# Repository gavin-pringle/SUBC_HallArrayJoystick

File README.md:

# SUBC - Hall-Effect Sensor Array Joystick

## Use Case

- For use in pilot's joystick controlling pitch and yaw for [SUBC](subc.ca)'s 2023 human powered submarine.
- A 3D printed assembly is being designed to house and guide a magnet to travel along the up-down and left-right axes of the PCBA. This magnet is connected to a joystick handle that is contrained to move along these same axes. When the pilot positions the magnet in a certain direction the magnet activates the hall-effect sensors in that direction. The quad op-amp IC in the center of the PCB produces a weighted average of the hall-effect outputs for each direction, weighting greater the sensor further from the center. Each output from the op-amp IC is connected to its labelled output pin in the JST connector.
- This design allows for easier waterproofing by excluding the use of potentiometers.

## Technical Specifications

- Two layer PCB, 100x100mm.
- Uses eight [DRV5055 SMD linear hall-effect sensors](https://www.ti.com/lit/ds/symlink/drv5055.pdf).
- Uses an [SMD quad op-amp](https://www.ti.com/lit/ds/symlink/lm2902-n.pdf) to average both hall-effect outputs in each direction (up, down, left, right).
- Single six pin JST connector containing PWR, GND, and analog outputs for each direction.
- Since connector is only through-hole component, entire PCBA can be easily waterproofed with potting compound for use in submarine.
- Current revision has extra traces and pads for optionally adding trimmer pots to tune hall effect sensor weighting.

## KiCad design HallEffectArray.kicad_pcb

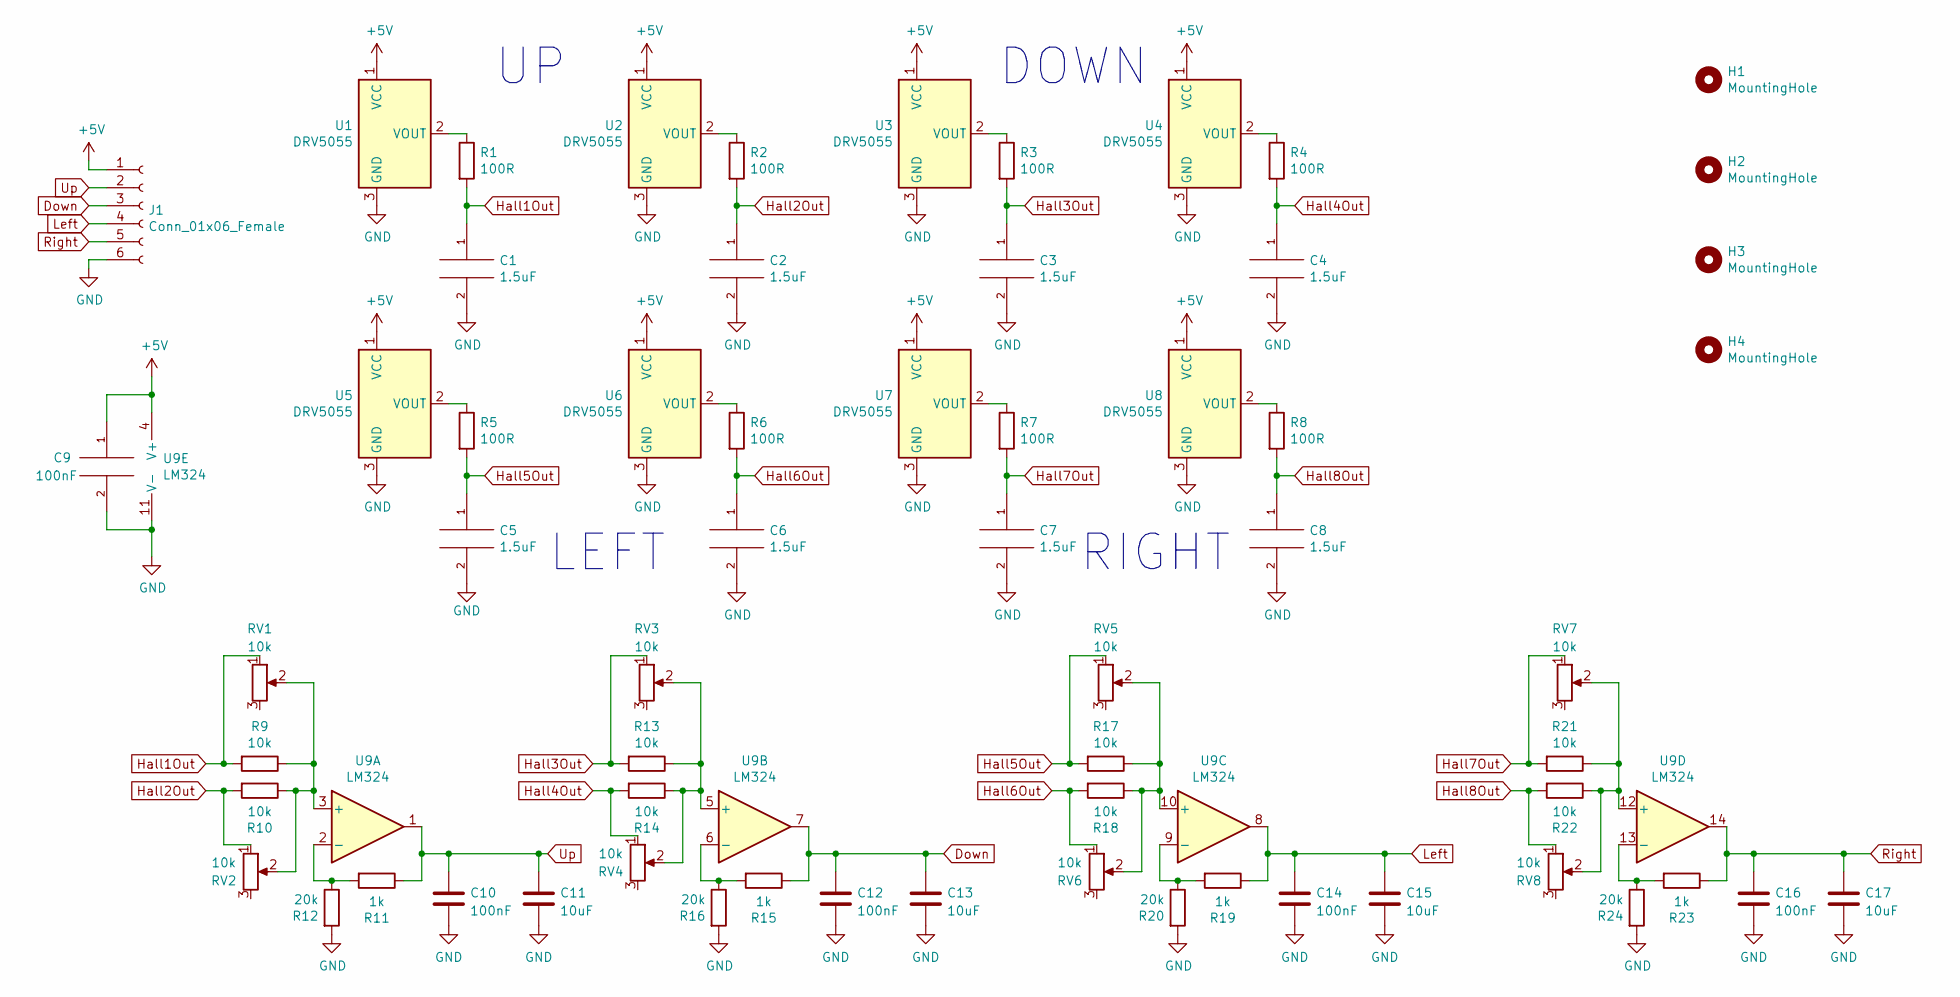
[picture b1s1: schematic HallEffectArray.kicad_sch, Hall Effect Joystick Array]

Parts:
C1, C2, C3, C4, C5, C6, C7, C8: 1.5uF; C_0805_2012Metric
C9, C10, C12, C14, C16: 100nF; C_0805_2012Metric
C11, C13, C15, C17: 10uF; C_0805_2012Metric
H1, H2, H3, H4: MountingHole; MountingHole_2.7mm_M2.5
J1: Conn_01x06_Female; JST_XH_B6B-XH-A_1x06_P2.50mm_Vertical
R1, R2, R3, R4, R5, R6, R7, R8: 100R; R_0805_2012Metric
R9, R10, R13, R14, R17, R18, R21, R22: 10k; R_0805_2012Metric
R11, R15, R19, R23: 1k; R_0805_2012Metric
R12, R16, R20, R24: 20k; R_0805_2012Metric
RV1, RV2, RV3, RV4, RV5, RV6, RV7, RV8: 10k; Potentiometer_Bourns_TC33X_Vertical
U1, U2, U3, U4, U5, U6, U7, U8: DRV5055; SOT-23
U9: LM324; SOIC-14_3.9x8.7mm_P1.27mm

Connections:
+5V: C9.1, J1.1, U1.1 (VCC), U2.1 (VCC), U3.1 (VCC), U4.1 (VCC), U5.1 (VCC), U6.1 (VCC), U7.1 (VCC), U8.1 (VCC), U9.4 (V+)
Down: C12.1, C13.1, J1.3, R15.1, U9.7
GND: C1.2, C2.2, C3.2, C4.2, C5.2, C6.2, C7.2, C8.2, C9.2, C10.2, C11.2, C12.2, C13.2, C14.2, C15.2, C16.2, C17.2, J1.6, R12.2, R16.2, R20.2, R24.2, U1.3 (GND), U2.3 (GND), U3.3 (GND), U4.3 (GND), U5.3 (GND), U6.3 (GND), U7.3 (GND), U8.3 (GND), U9.11 (V-)
Hall1Out: C1.1, R1.2, R9.2, RV1.1
Hall2Out: C2.1, R2.2, R10.2, RV2.1
Hall3Out: C3.1, R3.2, R13.2, RV3.1
Hall4Out: C4.1, R4.2, R14.2, RV4.1
Hall5Out: C5.1, R5.2, R17.2, RV5.1
Hall6Out: C6.1, R6.2, R18.2, RV6.1
Hall7Out: C7.1, R7.2, R21.2, RV7.1
Hall8Out: C8.1, R8.2, R22.2, RV8.1
Left: C14.1, C15.1, J1.4, R19.1, U9.8
unnamed: R1.1, U1.2 (VOUT)
unnamed: R2.1, U2.2 (VOUT)
unnamed: R3.1, U3.2 (VOUT)
unnamed: R4.1, U4.2 (VOUT)
unnamed: R5.1, U5.2 (VOUT)
unnamed: R6.1, U6.2 (VOUT)
unnamed: R7.1, U7.2 (VOUT)
unnamed: R8.1, U8.2 (VOUT)
unnamed: R9.1, R10.1, RV1.2, RV2.2, U9.3 (+)
unnamed: R11.2, R12.1, U9.2 (-)
unnamed: R13.1, R14.1, RV3.2, RV4.2, U9.5 (+)
unnamed: R15.2, R16.1, U9.6 (-)
unnamed: R17.1, R18.1, RV5.2, RV6.2, U9.10 (+)
unnamed: R19.2, R20.1, U9.9 (-)
unnamed: R21.1, R22.1, RV7.2, RV8.2, U9.12 (+)
unnamed: R23.2, R24.1, U9.13 (-)
Right: C16.1, C17.1, J1.5, R23.1, U9.14
Up: C10.1, C11.1, J1.2, R11.1, U9.1

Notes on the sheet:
DOWN
RIGHT
LEFT

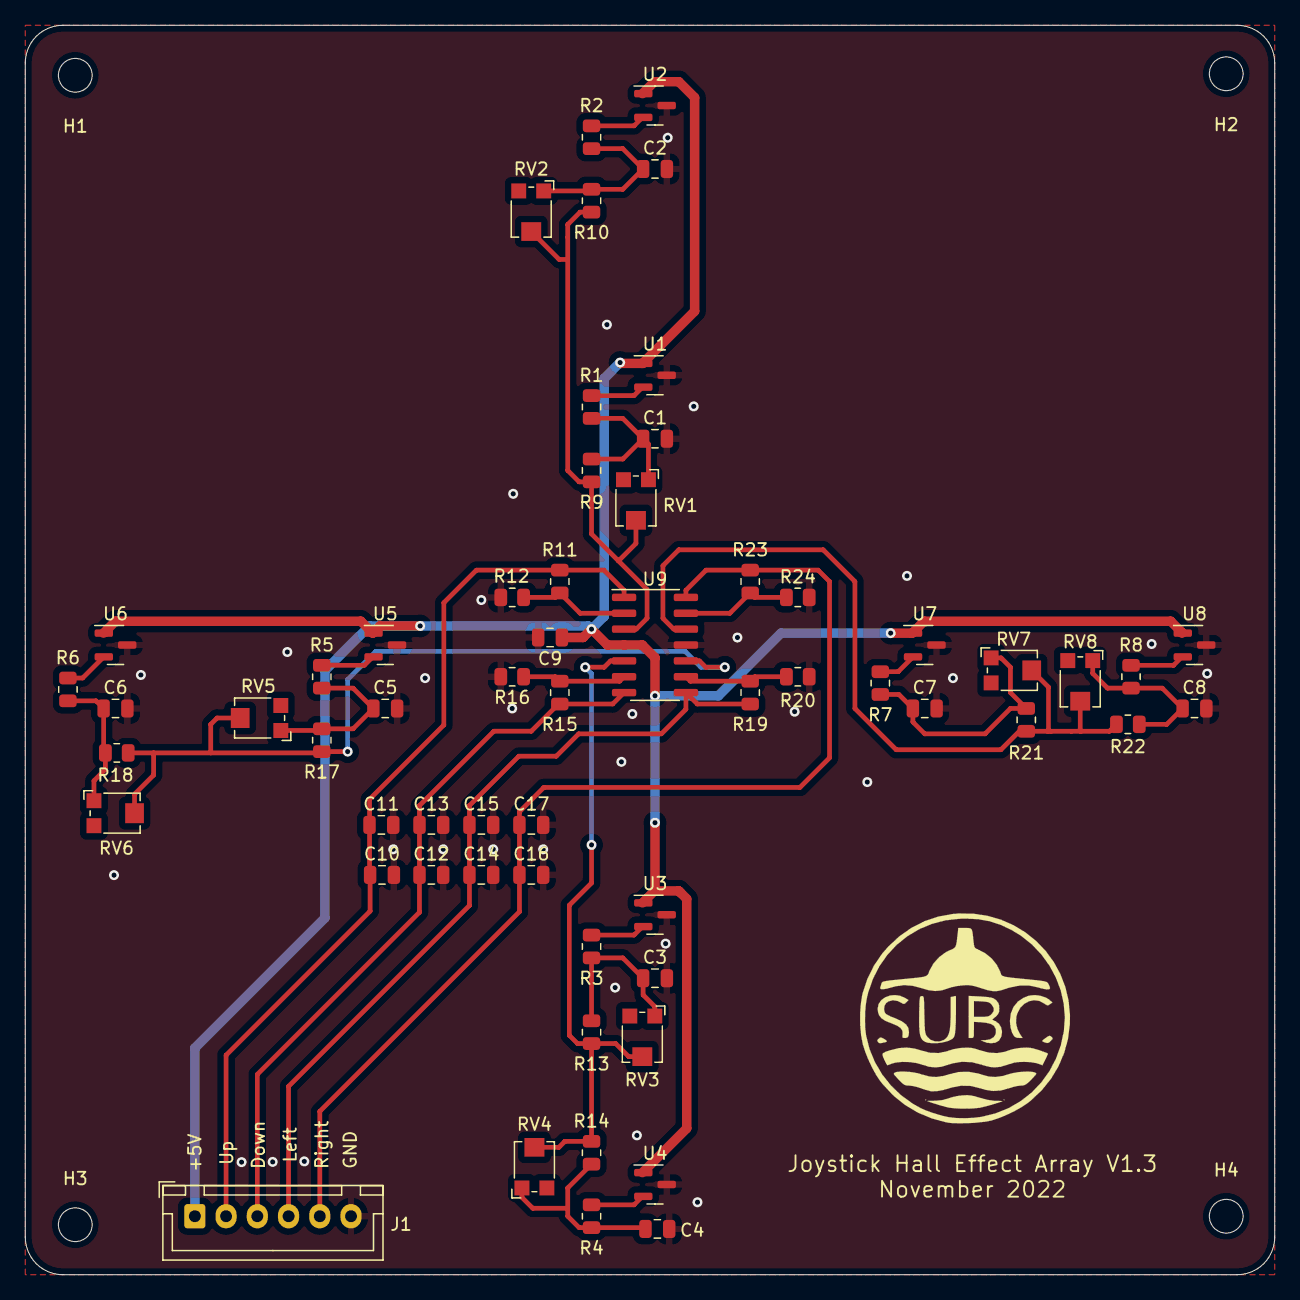
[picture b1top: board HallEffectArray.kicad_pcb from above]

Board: 2 copper layers, 100.0 x 100.0 mm, 63 parts (0 on the bottom side), 30 nets.

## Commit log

2022-10-22 v1.1, traces adjusted
2022-11-06 Deleted unchanged files from older version of Kicad
2022-11-06 Version 1.2: Added trimmer pots, bypass capacitors, vias, board size now 100x100mm
2022-11-20 V1.3: Added decoupling caps on outputs, more vias, changed datasheet
2023-01-05 Modified backups
2023-01-07 Added 3D render of PCB
2023-01-07 Added schematic screenshot
